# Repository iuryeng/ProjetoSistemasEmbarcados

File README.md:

# ProjetoSistemasEmbarcados - Controle de temperatuda com PID e Atmega328p 
repositório destinado ao projeto de sistemas embarcados. 

Equipe: Victor Perone e Iury Coelho

### Propósito

O controle da temperatura feito de maneira adequada é indispensável para uma melhor eficiência em processos que utilizam a temperatura como parâmetro. A idéia essencial de um dispositivo controlador de temperatura é medir e ajustar a temperatura através da experimentação e correção.  Uma solução viável para este tipo de problema é o uso de sistemas embarcados. 
Os sistemas embarcados têm se tornado cada vez mais utilizados como controladores de temperatura além de serem capazes de oferecer maior eficiência, baixo consumo energético e uma maior acessibilidade econômica. 

Esses sistemas possuem dispositivos de processamento e atuadores capazes de controlar processos e medir  parâmetros que podem  interferir na eficiência de aquecimento.  
Dessa forma, é possível processar dados de leitura da temperatura e compará-la com uma valor de referência e atuar no ajuste necessário. 
A técnica de controle PID (Proporcional, Integral e Derivativo) é uma das técnicas de controle mais utilizadas e pode ser implementada via lógica computacional em um sistema embarcado. O controle PID consiste em estabilizar um valor específico a partir de uma variável de interesse ou ponto de referência. A partir desse tipo de controle é possível responder a um tipo de variação da temperatura por meio de uma correção significativa associada ao erro calculado entre a interação sistema/meio físico e o valor de referência ou set point.

### Como usar este projeto 

- 1. abra o arquivo de simulação no proteus;
- 2. baixe o firmware em HEX
- 3. compile o firmware no Atmega328p
- 4. vizualise o controle da temperatura do aquecedor na simulação

- para entender o funcionamento acesse o link: https://www.youtube.com/watch?v=PiqRUjS0RfQ
- para ver a demonstração acesse o link: https://www.youtube.com/watch?v=kBlJRyW9vv4

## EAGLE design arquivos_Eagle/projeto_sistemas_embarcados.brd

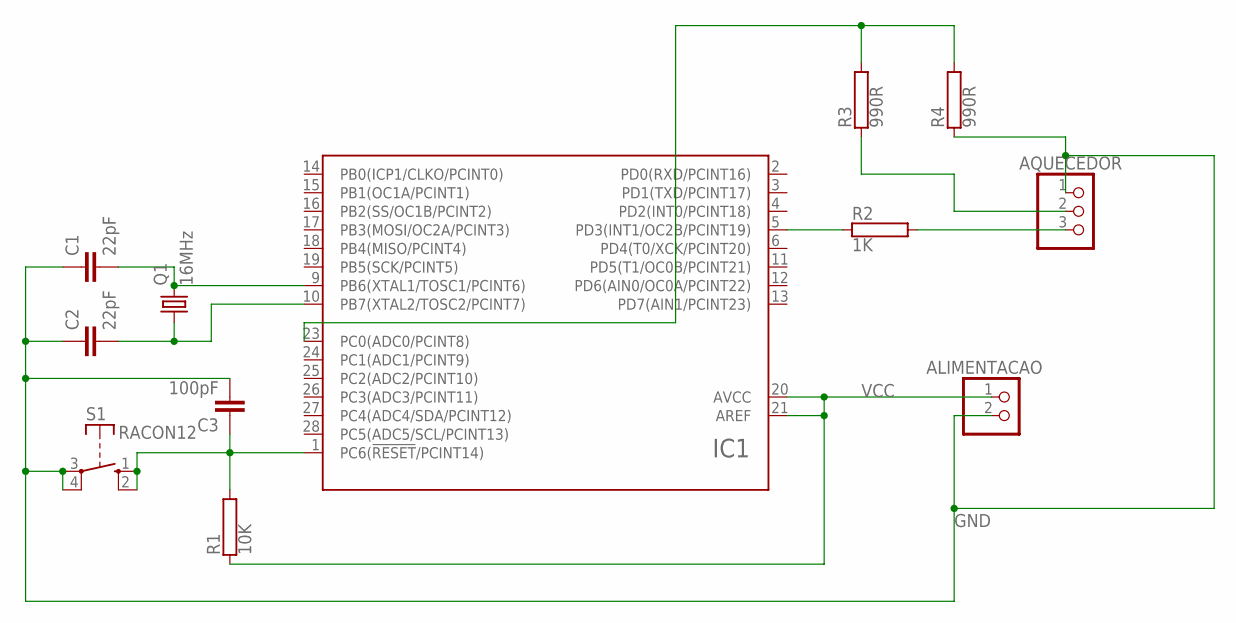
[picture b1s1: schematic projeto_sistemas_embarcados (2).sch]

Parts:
ALIMENTACAO: PINHD-1X2; 1X02
AQUECEDOR: PINHD-1X3; 1X03
C1, C2: 22pF; C2.5-3
C3: 100pF; C2.5-3
IC1: ATMEGA48/88/168/328-PU(DIP28)PU; DIL28
Q1: 16MHz; HC49/S
R1: 10K; AC01
R2: 1K; AC01
R3: 990R; HPS63
R4: 990R; AC01
S1: RACON12

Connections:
GND: ALIMENTACAO.2, AQUECEDOR.1, C1.1, C2.1, C3.2, IC1.8 (GND), IC1.22 (GND), R4.1, S1.3, S1.4
unnamed: AQUECEDOR.3, R2.2
unnamed: C1.2, IC1.9 (PB6(XTAL1/TOSC1/PCINT6)), Q1.2
unnamed: C2.2, IC1.10 (PB7(XTAL2/TOSC2/PCINT7)), Q1.1
unnamed: C3.1, IC1.1 (PC6(!RESET!/PCINT14)), R1.2, S1.1 (S), S1.2 (S)
unnamed: AQUECEDOR.2, R3.1
unnamed: IC1.5 (PD3(INT1/OC2B/PCINT19)), R2.1
unnamed: IC1.23 (PC0(ADC0/PCINT8)), R3.2, R4.2
UCC: IC1.7 (UCC)
VCC: ALIMENTACAO.1, IC1.20 (AVCC), IC1.21 (AREF), R1.1

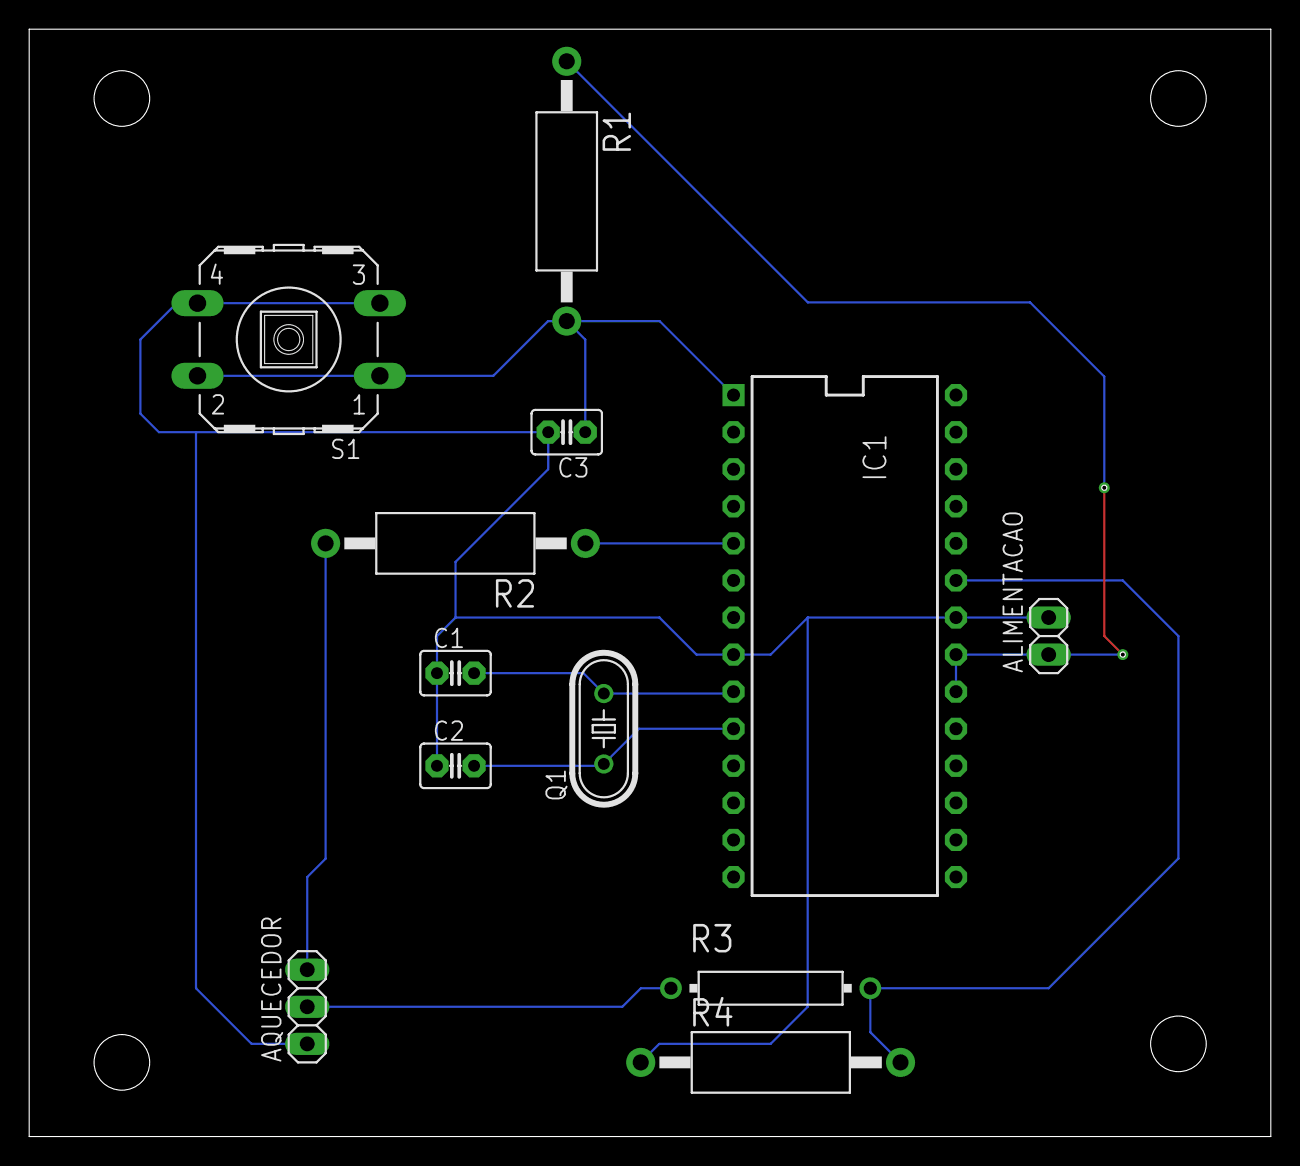
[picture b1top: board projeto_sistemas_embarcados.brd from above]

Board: 2 copper layers, 85.1 x 75.9 mm, 12 parts (0 on the bottom side), 9 nets.

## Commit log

2021-05-25 Firmware em Hexadecimal
2021-05-25 demonstração em video da simulação
2021-05-29 codigo pid escrito em c++
2021-05-29 add link com video no youtube
2021-05-29 readme com link de videos no youtube
2021-05-29 arquivos Eagle
2021-05-29 código final em c ++ corrigido
2021-05-29 add videos no youtube
2021-05-29 Correção readme
